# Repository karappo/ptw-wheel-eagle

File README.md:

# Eagle files for the board attached to the wheel of PlayTheWheels

## Related Projects

This project operate with these projects.

- [PlayTheWheels](https://github.com/karappo/PlayTheWheels)
- [ptw-wheel](https://github.com/karappo/ptw-wheel)

## Requiements

- [konashi Hardware Libraries](https://github.com/YUKAI/konashi-hardware)
- [ArduinoNanoV30](https://www.diymodules.org/eagle-show-library?type=usr&id=1012211674&part=ArduinoNano%2FArduinoNanoV30.lbr)

## Other parts

- [基板用マイクロＵＳＢコネクタ（電源専用）\[MRUSB-2B-D14NI-S306\]](http://akizukidenshi.com/catalog/g/gC-10398/)
- [トグルスイッチ（基板実装、小型タイプ）【5個入り】 (MTS-12PH-5P)](https://jp.misumi-ec.com/vona2/detail/110400372630/?HissuCode=MTS-12PH-5P) /5(1 unit)
- [ピンヘッダ（Ｌ型）1×6（6P）](http://akizukidenshi.com/catalog/g/gC-05336/) /2(3P) for LED-tape
- [ピンソケット（メス）1ｘ15（15Ｐ）](http://akizukidenshi.com/catalog/g/gC-10102/) x2 for Arduino
- [細ピンヘッダ　1×10](http://akizukidenshi.com/catalog/g/gC-04396/) x2 for Konashi

## License

All source code by Karappo Inc. (except files under `lib/ArduinoNanoV30` directory) are released under the MIT license.

https://raw.githubusercontent.com/karappo/ptw-wheel-eagle/master/LICENSE.txt

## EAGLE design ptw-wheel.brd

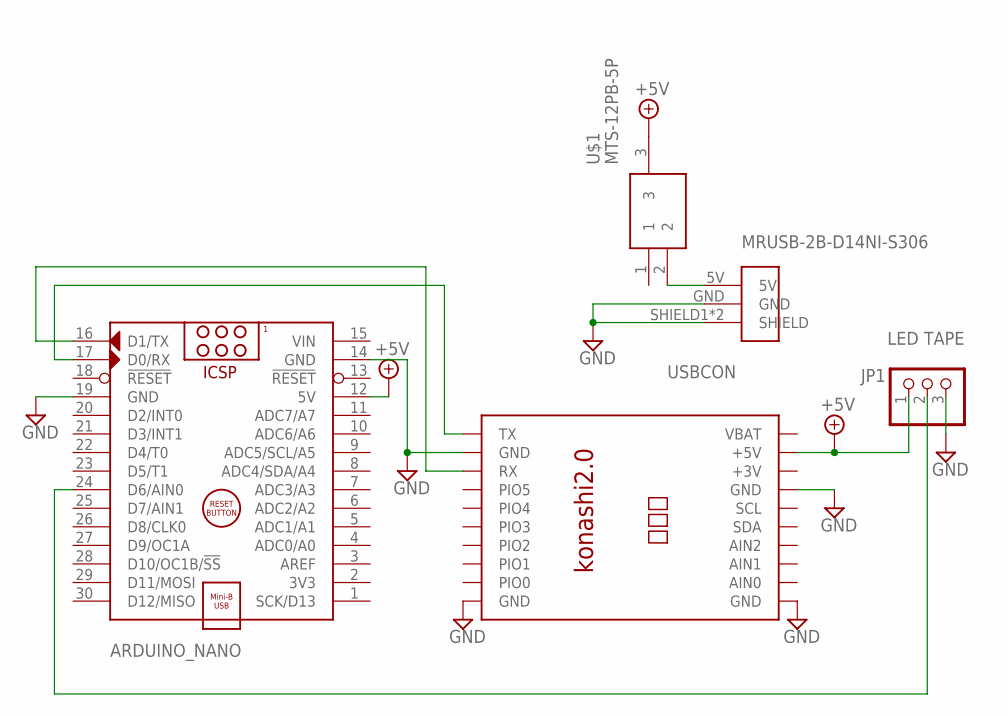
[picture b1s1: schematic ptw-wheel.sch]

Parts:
ARDUINO_NANO: ARDUINO_NANO
JP1: LED TAPE; 1X03
KONASHI: KONASHI2.0; KONASHI
MRUSB-2B-D14NI-S306: USBCON
U$1: MTS-12PB-5P

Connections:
+3V: KONASHI.+3V
+5V: ARDUINO_NANO.12 (5V), JP1.1, KONASHI.+5V, U$1.3
GND: ARDUINO_NANO.14 (GND), ARDUINO_NANO.19 (GND), JP1.3, KONASHI.GND, KONASHI.GND@1 (GND), KONASHI.GND@2 (GND), KONASHI.GND@3 (GND), MRUSB-2B-D14NI-S306.GND, MRUSB-2B-D14NI-S306.SHIELD1 (SHIELD), MRUSB-2B-D14NI-S306.SHIELD2 (SHIELD)
unnamed: MRUSB-2B-D14NI-S306.5V, U$1.2
unnamed: ARDUINO_NANO.24 (D6/AIN0), JP1.2
unnamed: ARDUINO_NANO.17 (D0/RX), KONASHI.TX
unnamed: ARDUINO_NANO.16 (D1/TX), KONASHI.RX
VBAT: KONASHI.VBAT
VIN: ARDUINO_NANO.15 (VIN)

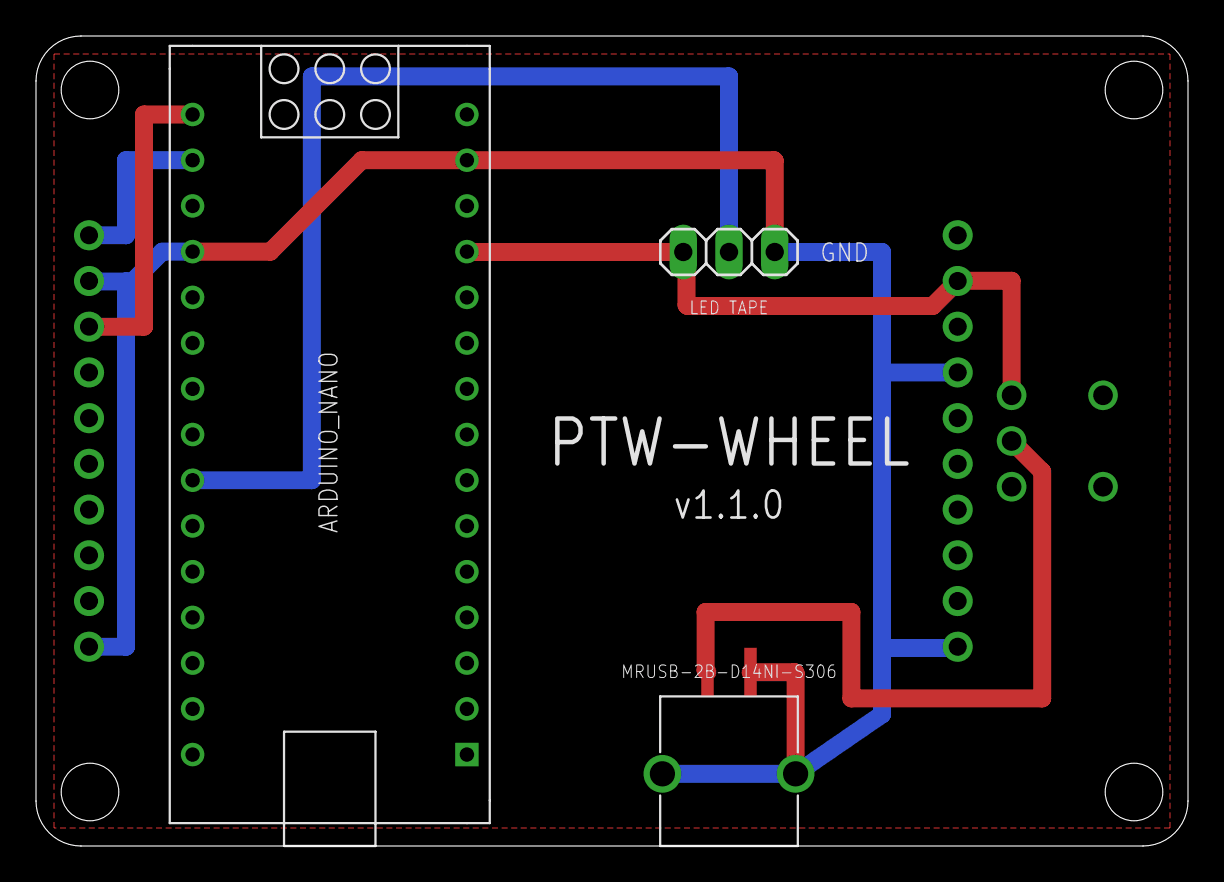
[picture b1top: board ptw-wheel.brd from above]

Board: 2 copper layers, 64.0 x 45.0 mm, 5 parts (1 on the bottom side), 6 nets.

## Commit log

2019-04-16 Remove unnecessary files
2019-04-16 Add LICESE and README
2019-04-16 Fix path
2019-05-05 - Add konashi official lbr file - Remove unnecessary lbr files - Update README to rewrite requirement
2019-05-07 Create board data
2019-05-08 Add text
2019-05-08 Replace GND to N$1 ?
2019-05-08 Export NetScript file and import it on the brd file
2019-05-08 Rename connection to 'GND'
2019-05-08 Change grid setting
2019-05-08 Move konashi position
2019-05-08 Fix grid setting
2019-05-08 GNDがAirwireになっているのを解消できた！
2019-05-08 Fix typo
2019-05-08 Konashiの位置調整もするのでリネーム
2019-05-13 ボードのレイアウト整理
2019-05-13 トグルスイッチのライブラリを下記からDLLした型違いのlbrを元に修正して
    https://componentsearchengine.com/2MS1-T1-B4-M2-Q-E/Cosland
2019-05-13 トグルスイッチを追加
2019-06-03 ライブラリの更新（Konashiのアウトラインは背面にするなど）
2019-06-03 - Rename lbr before adding new device - Remove old lbr
2019-06-03 - Replace toggle switch - Adjust positions
2019-06-03 Adjust position of USBcon and LED tapes to avoid confliction with foots
2019-06-03 Move switch position
2019-06-04 Change board size to 45x64 (same as DAISEN's)
2019-06-04 Round edges
2019-06-04 Hide unnecessary infomations
2019-06-04 Update konashi lib
2019-06-04 Modify texts
2019-06-04 Change layout of board title
2019-06-04 - Write down module names - Modify layout
2019-06-04 Set layer visiblity
2019-06-04 Remove bar
2019-06-04 not sure
2019-06-18 Add 'Other parts'
2019-06-18 Modify parts count
2019-07-06 Change repo name
